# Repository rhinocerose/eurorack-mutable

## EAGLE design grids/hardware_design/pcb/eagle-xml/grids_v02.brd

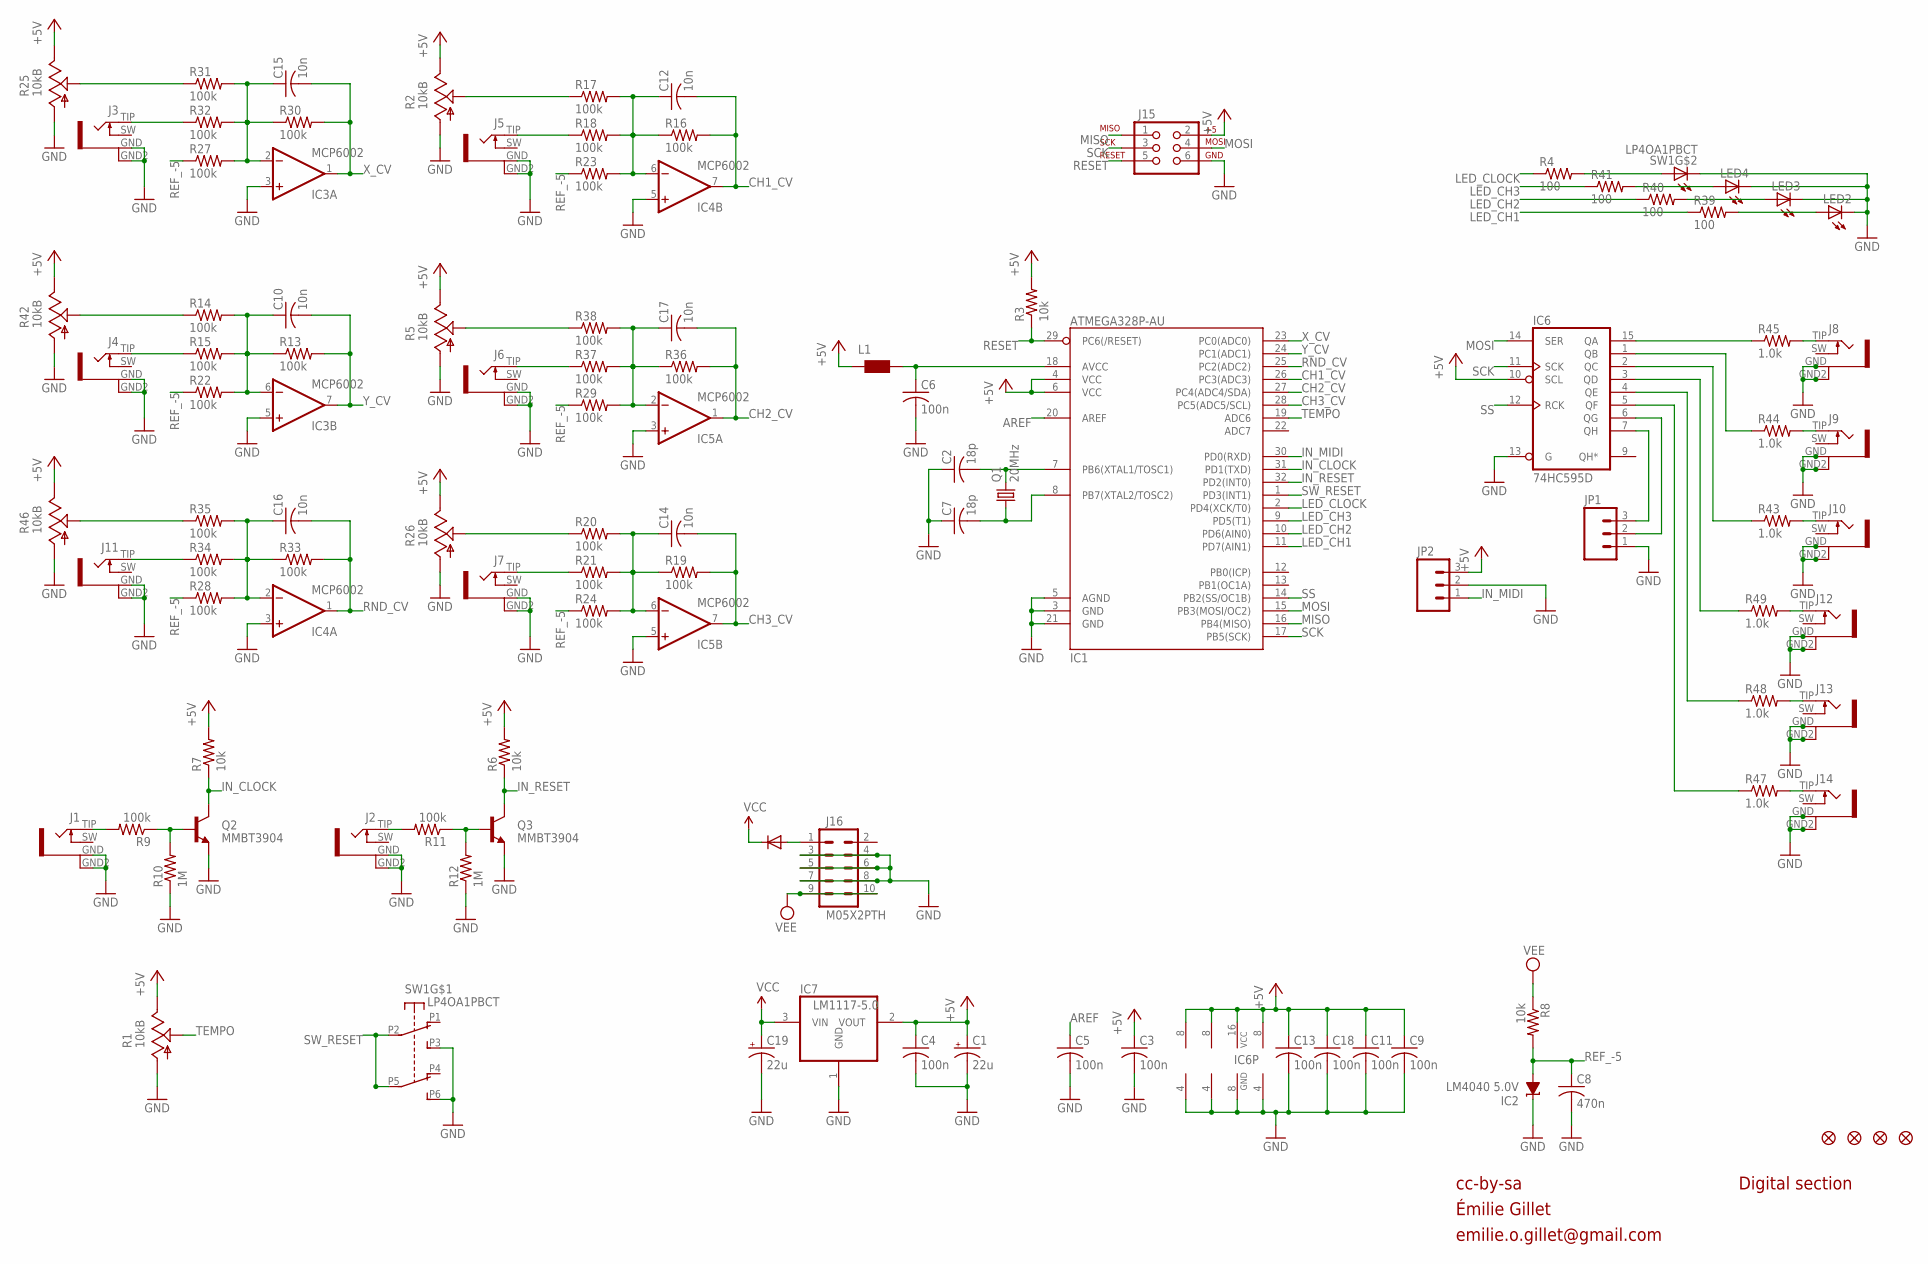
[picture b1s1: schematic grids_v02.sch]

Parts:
C1, C19: 22u; PANASONIC_C
C2, C7: 18p; C0603
C3, C4, C5, C6, C9, C11, C13, C18: 100n; C0603
C8: 470n; C0603
C10, C12, C14, C15, C16, C17: 10n; C0603
D1: 1N5819HW; SOD123
F1, F2, F3, F4: FIDUCIAL1X2; FIDUCIAL-1X2
IC1: ATMEGA328P-AU; TQFP32-08
IC2: LM4040 5.0V; DBZ_R-PDSO-G3
IC3, IC4, IC5: MCP6002; SO08
IC6: 74HC595D; SO16
IC7: LM1117-5.0; SOT223
J1, J2, J3, J4, J5, J6, J7, J8, J9, J10, J11, J12, J13, J14: PJ301WQP; WQP_PJ_301BM
J15: AVR_SPI_PRG_6PTH; 2X3
J16: M05X2PTH; AVR_ICSP
JP1, JP2: M03PTH; 1X03
L1: WE-CBF_0603; 0603
LED2, LED3, LED4: LED3MM
Q1: 20MHz; HC49UP
Q2, Q3: MMBT3904; SOT23-BEC
R1, R2, R5, R25, R26, R46: 10kB; ALPS_POT_VERTICAL_PS
R3, R6, R7, R8: 10k; R0603
R4, R39, R40, R41: 100; R0603
R9, R11, R13, R14, R15, R16, R17, R18, R19, R20, R21, R22, R23, R24, R27, R28, R29, R30, R31, R32, R33, R34, R35, R36, R37, R38: 100k; R0603
R10, R12: 1M; R0603
R42: 10kB; ALPS_POT_VERTICAL_PS4
R43, R44, R45, R47, R48, R49: 1.0k; R0603
SW1: LP4OA1PBCT

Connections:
+5V: C1.+, C3.1, C4.1, C9.1, C11.1, C13.1, C18.1, IC1.4 (VCC), IC1.6 (VCC), IC3.8 (V+), IC4.8 (V+), IC5.8 (V+), IC6.10 (SCL), IC6.16 (VCC), IC7.2 (VOUT), J15.2, JP2.3, L1.1, R1.P$1 (E), R2.P$1 (E), R3.2, R5.P$1 (E), R6.2, R7.2, R25.P$1 (E), R26.P$1 (E), R42.P$1 (E), R46.P$1 (E)
AREF: C5.1, IC1.20 (AREF)
CH1_CV: C12.2, IC1.26 (PC3(ADC3)), IC4.7 (OUT), R16.2
CH2_CV: C17.2, IC1.27 (PC4(ADC4/SDA)), IC5.1 (OUT), R36.2
CH3_CV: C14.2, IC1.28 (PC5(ADC5/SCL)), IC5.7 (OUT), R19.2
CLOCK_OUT: IC6.6 (QG), JP1.2
GATE1_IN: J1.TIP (2), R9.2
GATE1_LED: R4.2, SW1.L1
GATE2_IN: J2.TIP (2), R11.2
GATE2_LED: LED4.A, R41.2
GATE3_LED: LED3.A, R40.2
GATE4_LED: LED2.A, R39.2
GND: C1.-, C2.1, C3.2, C4.2, C5.2, C6.2, C7.1, C8.2, C9.2, C11.2, C13.2, C18.2, C19.-, IC1.3 (GND), IC1.5 (AGND), IC1.21 (GND), IC2.1 (C), IC3.3 (+IN), IC3.4 (V-), IC3.5 (+IN), IC4.3 (+IN), IC4.4 (V-), IC4.5 (+IN), IC5.3 (+IN), IC5.4 (V-), IC5.5 (+IN), IC6.8 (GND), IC6.13 (G), IC7.1 (GND), J1.GND (1), J1.GND2 (4), J2.GND (1), J2.GND2 (4), J3.GND (1), J3.GND2 (4), J4.GND (1), J4.GND2 (4), J5.GND (1), J5.GND2 (4), J6.GND (1), J6.GND2 (4), J7.GND (1), J7.GND2 (4), J8.GND (1), J8.GND2 (4), J9.GND (1), J9.GND2 (4), J10.GND (1), J10.GND2 (4), J11.GND (1), J11.GND2 (4), J12.GND (1), J12.GND2 (4), J13.GND (1), J13.GND2 (4), J14.GND (1), J14.GND2 (4), J15.6, J16.3, J16.4, J16.5, J16.6, J16.7, J16.8, JP1.1, JP2.2, LED2.K (C), LED3.K (C), LED4.K (C), Q2.E, Q3.E, R1.P$3 (A), R2.P$3 (A), R5.P$3 (A), R10.1, R12.1, R25.P$3 (A), R26.P$3 (A), R42.P$3 (A), R46.P$3 (A), SW1.L2, SW1.P3 (A3), SW1.P6 (B3)
IN_CLOCK: IC1.31 (PD1(TXD)), Q2.C, R7.1
IN_MIDI: IC1.30 (PD0(RXD)), JP2.1
IN_RESET: IC1.32 (PD2(INT0)), Q3.C, R6.1
LED_CH1: IC1.11 (PD7(AIN1)), R39.1
LED_CH2: IC1.10 (PD6(AIN0)), R40.1
LED_CH3: IC1.9 (PD5(T1)), R41.1
LED_CLOCK: IC1.2 (PD4(XCK/T0)), R4.1
MISO: IC1.16 (PB4(MISO)), J15.1
MOSI: IC1.15 (PB3(MOSI/OC2)), IC6.14 (SER), J15.4
unnamed: Q2.B, R9.1, R10.2
unnamed: Q3.B, R11.1, R12.2
unnamed: D1.A, J16.1
unnamed: J14.TIP (2), R47.2
unnamed: J13.TIP (2), R48.2
unnamed: J12.TIP (2), R49.2
unnamed: R25.P$2 (S), R31.1
unnamed: J3.TIP (2), R32.1
unnamed: C10.1, IC3.6 (-IN), R13.1, R14.2, R15.2, R22.2
unnamed: R14.1, R42.P$2 (S)
unnamed: J4.TIP (2), R15.1
unnamed: C16.1, IC4.2 (-IN), R28.2, R33.1, R34.2, R35.2
unnamed: R35.1, R46.P$2 (S)
unnamed: J11.TIP (2), R34.1
unnamed: C12.1, IC4.6 (-IN), R16.1, R17.2, R18.2, R23.2
unnamed: R2.P$2 (S), R17.1
unnamed: J5.TIP (2), R18.1
unnamed: C17.1, IC5.2 (-IN), R29.2, R36.1, R37.2, R38.2
unnamed: R5.P$2 (S), R38.1
unnamed: J6.TIP (2), R37.1
unnamed: C14.1, IC5.6 (-IN), R19.1, R20.2, R21.2, R24.2
unnamed: R20.1, R26.P$2 (S)
unnamed: J7.TIP (2), R21.1
unnamed: IC6.15 (QA), R45.1
unnamed: IC6.1 (QB), R44.1
unnamed: C15.1, IC3.2 (-IN), R27.2, R30.1, R31.2, R32.2
unnamed: IC6.2 (QC), R43.1
unnamed: IC6.3 (QD), R49.1
unnamed: IC6.4 (QE), R48.1
unnamed: IC6.5 (QF), R47.1
unnamed: J8.TIP (2), R45.2
unnamed: J9.TIP (2), R44.2
unnamed: J10.TIP (2), R43.2
unnamed: C6.1, IC1.18 (AVCC), L1.2
unnamed: C7.2, IC1.8 (PB7(XTAL2/TOSC2)), Q1.1
unnamed: C2.2, IC1.7 (PB6(XTAL1/TOSC1)), Q1.2
RANDOM_GATE: IC6.7 (QH), JP1.3
REF_-5: C8.1, IC2.2 (A), R8.2, R22.1, R23.1, R24.1, R27.1, R28.1, R29.1
RESET: IC1.29 (PC6(/RESET)), J15.5, R3.1
RND_CV: C16.2, IC1.25 (PC2(ADC2)), IC4.1 (OUT), R33.2
SCK: IC1.17 (PB5(SCK)), IC6.11 (SCK), J15.3
SS: IC1.14 (PB2(SS/OC1B)), IC6.12 (RCK)
SW_RESET: IC1.1 (PD3(INT1)), SW1.P2 (A2), SW1.P5 (B2)
TEMPO: IC1.19 (ADC6), R1.P$2 (S)
VCC: C19.+, D1.C, IC7.3 (VIN)
VEE: J16.9, J16.10, R8.1
X_CV: C15.2, IC1.23 (PC0(ADC0)), IC3.1 (OUT), R30.2
Y_CV: C10.2, IC1.24 (PC1(ADC1)), IC3.7 (OUT), R13.2

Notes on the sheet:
cc-by-sa
Digital section
Émilie Gillet
emilie.o.gillet@gmail.com

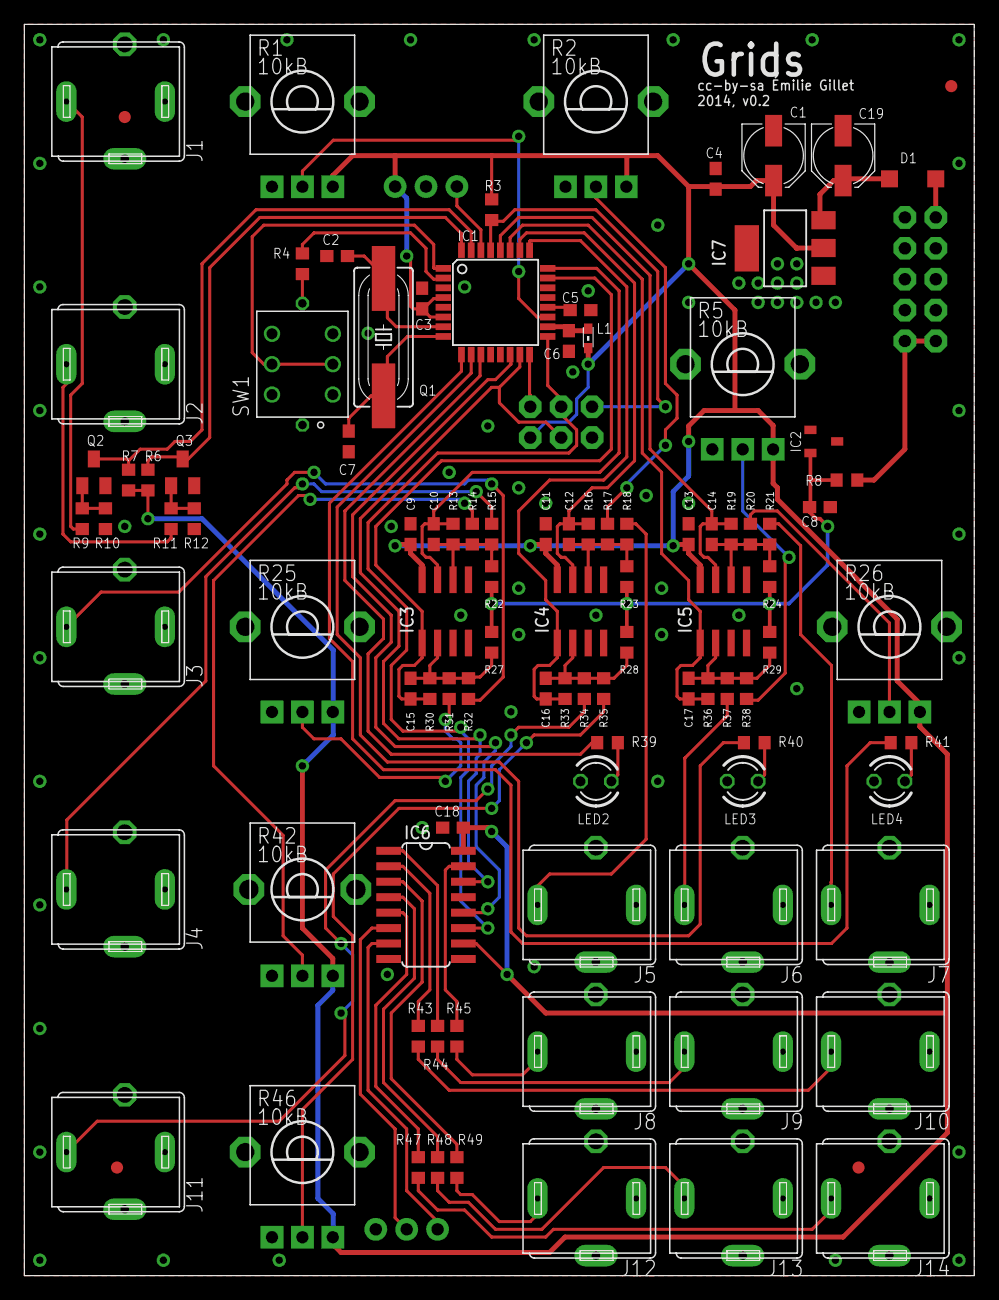
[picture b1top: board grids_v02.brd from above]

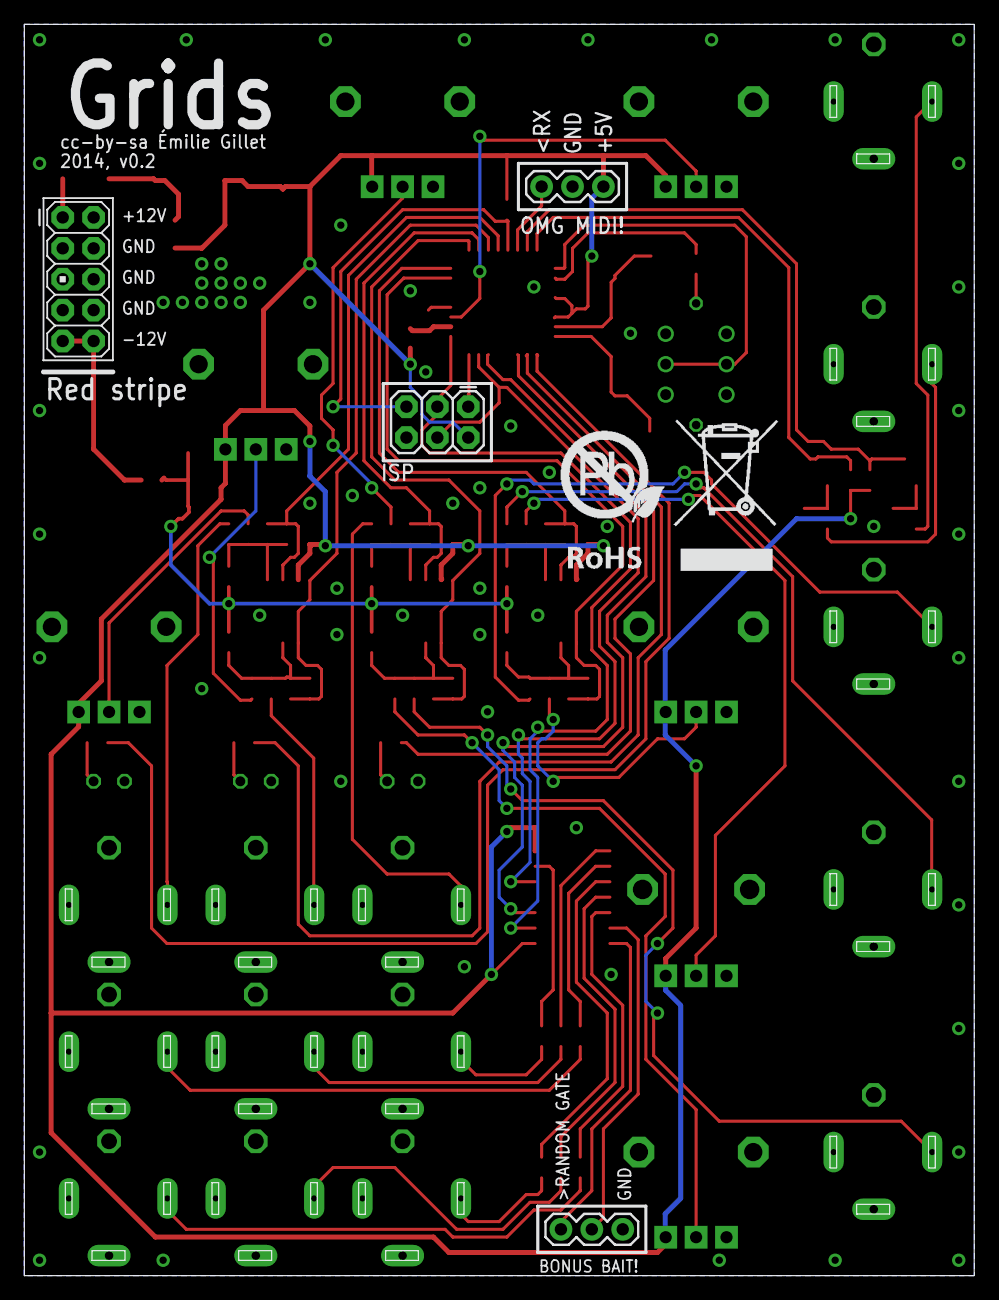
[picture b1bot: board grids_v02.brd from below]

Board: 2 copper layers, 78.1 x 102.9 mm, 108 parts (5 on the bottom side), 70 nets.

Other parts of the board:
U$1: EURORACK_TEMPLATE
U$2: ROHS_BIG

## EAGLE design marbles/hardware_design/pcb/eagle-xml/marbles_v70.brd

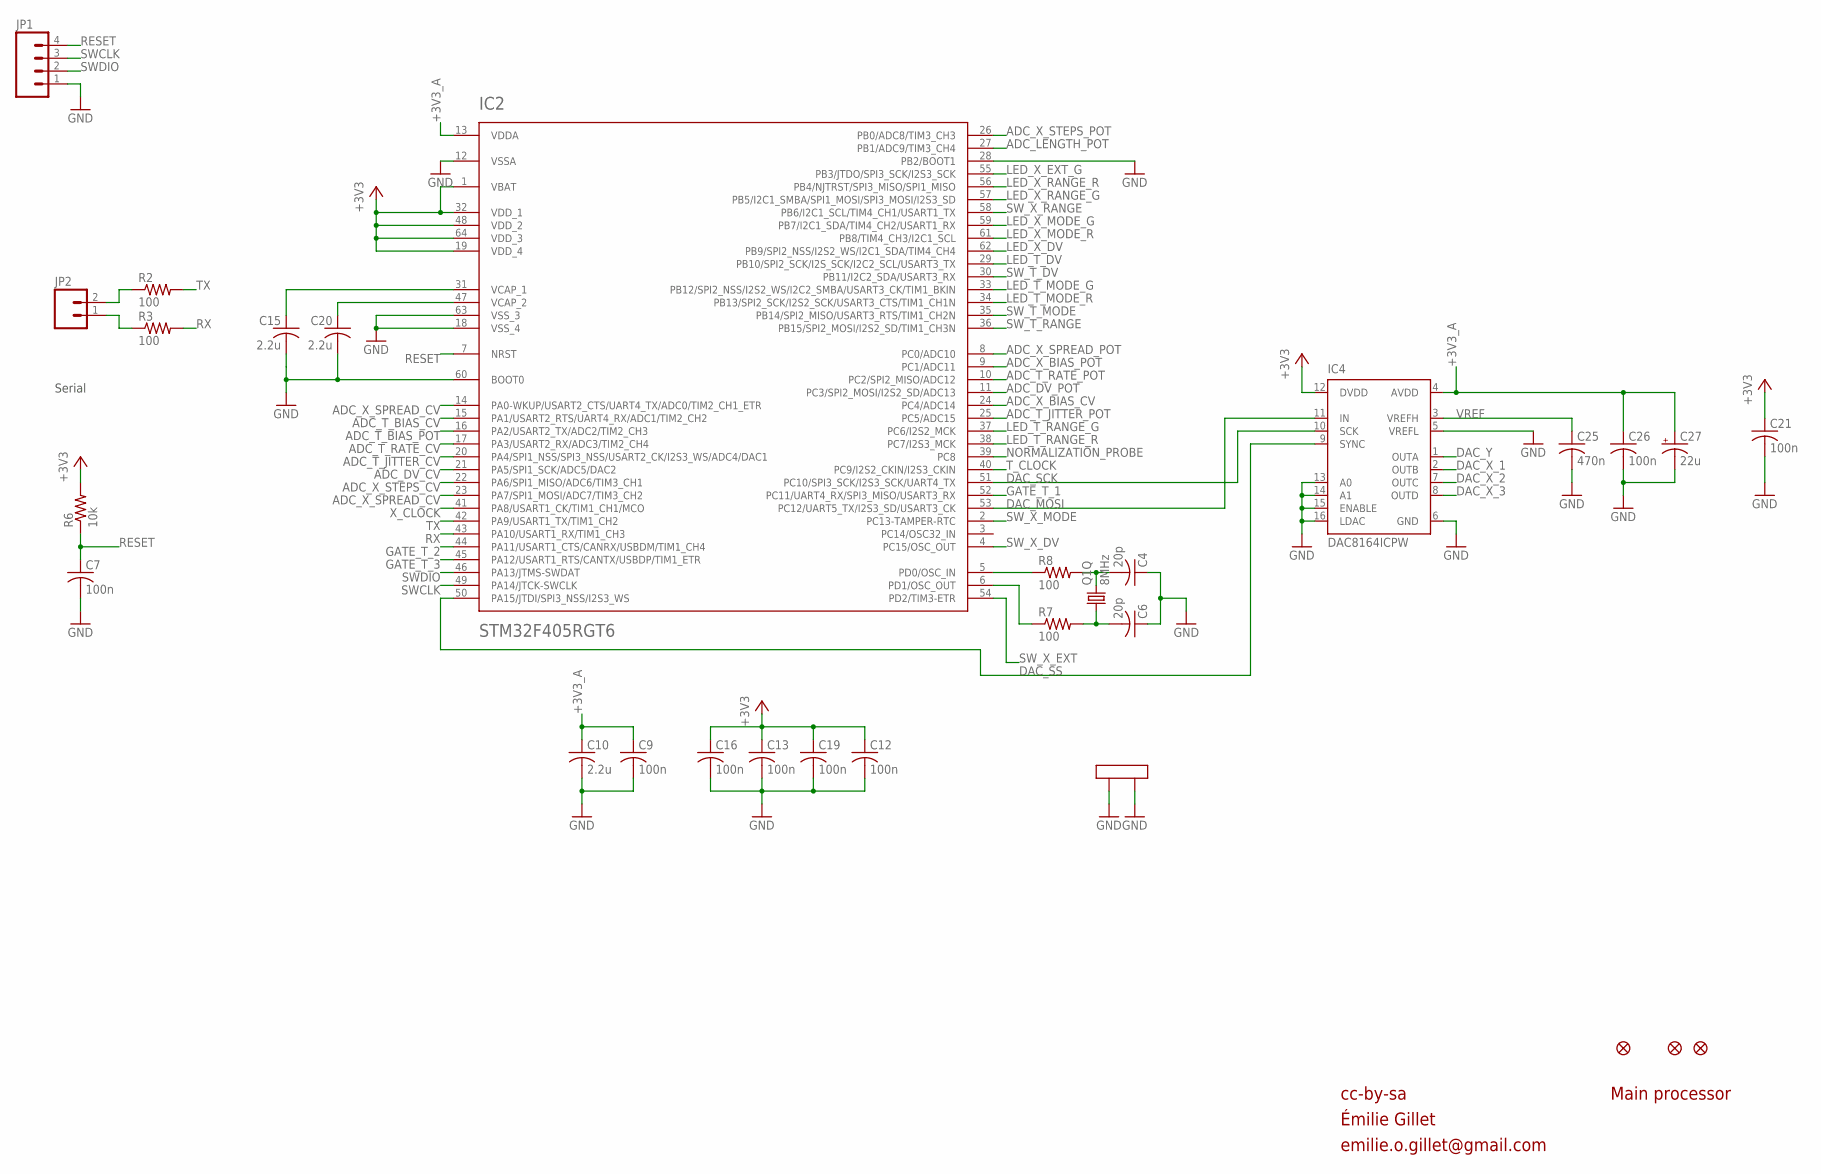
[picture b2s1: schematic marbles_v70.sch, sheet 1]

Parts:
C4, C6: 20p; C0402
C7, C9, C12, C13, C16, C19, C21, C26: 100n; C0402
C10, C15, C20: 2.2u; C0805
C25: 470n; C0402
C27: 22u; PANASONIC_C
F1, F2, F3: FIDUCIAL1X2; FIDUCIAL-1X2
IC2: STM32F405RGT6; TQFP-10X10-64
IC4: DAC8164ICPW; SOP65P640X110-16N
JP1: M04PTH; 1X04
JP2: M02PTH; 1X02
Q1: 8MHz; CTS406
R2, R3, R7, R8: 100; R0402
R6: 10k; R0402

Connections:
+3V3: C12.1, C13.1, C16.1, C19.1, C21.1, IC2.1 (VBAT), IC2.19 (VDD_4), IC2.32 (VDD_1), IC2.48 (VDD_2), IC2.64 (VDD_3), IC4.12 (DVDD), R6.2; also elsewhere on the board
+3V3_A: C9.1, C10.1, C26.1, C27.+, IC2.13 (VDDA), IC4.4 (AVDD); also elsewhere on the board
ADC_DV_CV: IC2.21 (PA5/SPI1_SCK/ADC5/DAC2); also elsewhere on the board
ADC_DV_POT: IC2.11 (PC3/SPI2_MOSI/I2S2_SD/ADC13); also elsewhere on the board
ADC_LENGTH_POT: IC2.27 (PB1/ADC9/TIM3_CH4); also elsewhere on the board
ADC_T_BIAS_CV: IC2.15 (PA1/USART2_RTS/UART4_RX/ADC1/TIM2_CH2); also elsewhere on the board
ADC_T_BIAS_POT: IC2.16 (PA2/USART2_TX/ADC2/TIM2_CH3); also elsewhere on the board
ADC_T_JITTER_CV: IC2.20 (PA4/SPI1_NSS/SPI3_NSS/USART2_CK/I2S3_WS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); also elsewhere on the board
ADC_T_JITTER_POT: IC2.25 (PC5/ADC15); also elsewhere on the board
ADC_T_RATE_CV: IC2.17 (PA3/USART2_RX/ADC3/TIM2_CH4); also elsewhere on the board
ADC_T_RATE_POT: IC2.10 (PC2/SPI2_MISO/ADC12); also elsewhere on the board
ADC_X_BIAS_CV: IC2.24 (PC4/ADC14); also elsewhere on the board
ADC_X_BIAS_POT: IC2.9 (PC1/ADC11); also elsewhere on the board
ADC_X_SPREAD_CV: IC2.14 (PA0-WKUP/USART2_CTS/UART4_TX/ADC0/TIM2_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), IC2.23 (PA7/SPI1_MOSI/ADC7/TIM3_CH2); also elsewhere on the board
ADC_X_SPREAD_POT: IC2.8 (PC0/ADC10); also elsewhere on the board
ADC_X_STEPS_CV: IC2.22 (PA6/SPI1_MISO/ADC6/TIM3_CH1); also elsewhere on the board
ADC_X_STEPS_POT: IC2.26 (PB0/ADC8/TIM3_CH3); also elsewhere on the board
DAC_MOSI: IC2.53 (PC12/UART5_TX/I2S3_SD/USART3_CK), IC4.11 (IN)
DAC_SCK: IC2.51 (PC10/SPI3_SCK/I2S3_SCK/UART4_TX), IC4.10 (SCK)
DAC_SS: IC2.50 (PA15/JTDI/SPI3_NSS/I2S3_WS), IC4.9 (SYNC)
DAC_X_1: IC4.2 (OUTB); also elsewhere on the board
DAC_X_2: IC4.7 (OUTC); also elsewhere on the board
DAC_X_3: IC4.8 (OUTD); also elsewhere on the board
DAC_Y: IC4.1 (OUTA); also elsewhere on the board
GATE_T_1: IC2.52 (PC11/UART4_RX/SPI3_MISO/USART3_RX); also elsewhere on the board
GATE_T_2: IC2.44 (PA11/USART1_CTS/CANRX/USBDM/TIM1_CH4); also elsewhere on the board
GATE_T_3: IC2.45 (PA12/USART1_RTS/CANTX/USBDP/TIM1_ETR); also elsewhere on the board
GND: C4.1, C6.1, C7.2, C9.2, C10.2, C12.2, C13.2, C15.2, C16.2, C19.2, C20.2, C21.2, C25.2, C26.2, C27.-, IC2.12 (VSSA), IC2.18 (VSS_4), IC2.28 (PB2/BOOT1), IC2.60 (BOOT0), IC2.63 (VSS_3), IC4.5 (VREFL), IC4.6 (GND), IC4.13 (A0), IC4.14 (A1), IC4.15 (ENABLE), IC4.16 (LDAC), JP1.1, Q1.2 (LID1), Q1.4 (LID2); also elsewhere on the board
LED_T_DV: IC2.29 (PB10/SPI2_SCK/I2S_SCK/I2C2_SCL/USART3_TX); also elsewhere on the board
LED_T_MODE_G: IC2.33 (PB12/SPI2_NSS/I2S2_WS/I2C2_SMBA/USART3_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); also elsewhere on the board
LED_T_MODE_R: IC2.34 (PB13/SPI2_SCK/I2S2_SCK/USART3_CTS/TIM1_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); also elsewhere on the board
LED_T_RANGE_G: IC2.37 (PC6/I2S2_MCK); also elsewhere on the board
LED_T_RANGE_R: IC2.38 (PC7/I2S3_MCK); also elsewhere on the board
LED_X_DV: IC2.62 (PB9/SPI2_NSS/I2S2_WS/I2C1_SDA/TIM4_CH4); also elsewhere on the board
LED_X_EXT_G: IC2.55 (PB3/JTDO/SPI3_SCK/I2S3_SCK); also elsewhere on the board
LED_X_MODE_G: IC2.59 (PB7/I2C1_SDA/TIM4_CH2/USART1_RX); also elsewhere on the board
LED_X_MODE_R: IC2.61 (PB8/TIM4_CH3/I2C1_SCL); also elsewhere on the board
LED_X_RANGE_G: IC2.57 (PB5/I2C1_SMBA/SPI1_MOSI/SPI3_MOSI/I2S3_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); also elsewhere on the board
LED_X_RANGE_R: IC2.56 (PB4/NJTRST/SPI3_MISO/SPI1_MISO); also elsewhere on the board
unnamed: IC2.6 (PD1/OSC_OUT), R7.1
unnamed: IC2.5 (PD0/OSC_IN), R8.1
unnamed: C20.1, IC2.47 (VCAP_2)
unnamed: C15.1, IC2.31 (VCAP_1)
unnamed: JP2.2, R2.1
unnamed: JP2.1, R3.1
unnamed: C4.2, Q1.3 (2), R8.2
unnamed: C6.2, Q1.1, R7.2
NORMALIZATION_PROBE: IC2.39 (PC8); also elsewhere on the board
RESET: C7.1, IC2.7 (NRST), JP1.4, R6.1
RX: IC2.43 (PA10/USART1_RX/TIM1_CH3), R3.2
SWCLK: IC2.49 (PA14/JTCK-SWCLK), JP1.3
SWDIO: IC2.46 (PA13/JTMS-SWDAT), JP1.2
SW_T_DV: IC2.30 (PB11/I2C2_SDA/USART3_RX); also elsewhere on the board
SW_T_MODE: IC2.35 (PB14/SPI2_MISO/USART3_RTS/TIM1_CH2N); also elsewhere on the board
SW_T_RANGE: IC2.36 (PB15/SPI2_MOSI/I2S2_SD/TIM1_CH3N); also elsewhere on the board
SW_X_DV: IC2.4 (PC15/OSC_OUT); also elsewhere on the board
SW_X_EXT: IC2.54 (PD2/TIM3-ETR); also elsewhere on the board
SW_X_MODE: IC2.2 (PC13-TAMPER-RTC); also elsewhere on the board
SW_X_RANGE: IC2.58 (PB6/I2C1_SCL/TIM4_CH1/USART1_TX); also elsewhere on the board
TX: IC2.42 (PA9/USART1_TX/TIM1_CH2), R2.2
T_CLOCK: IC2.40 (PC9/I2S2_CKIN/I2S3_CKIN); also elsewhere on the board
VREF: C25.1, IC4.3 (VREFH); also elsewhere on the board
X_CLOCK: IC2.41 (PA8/USART1_CK/TIM1_CH1/MCO); also elsewhere on the board

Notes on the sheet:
cc-by-sa
Main processor
Serial
Émilie Gillet
emilie.o.gillet@gmail.com

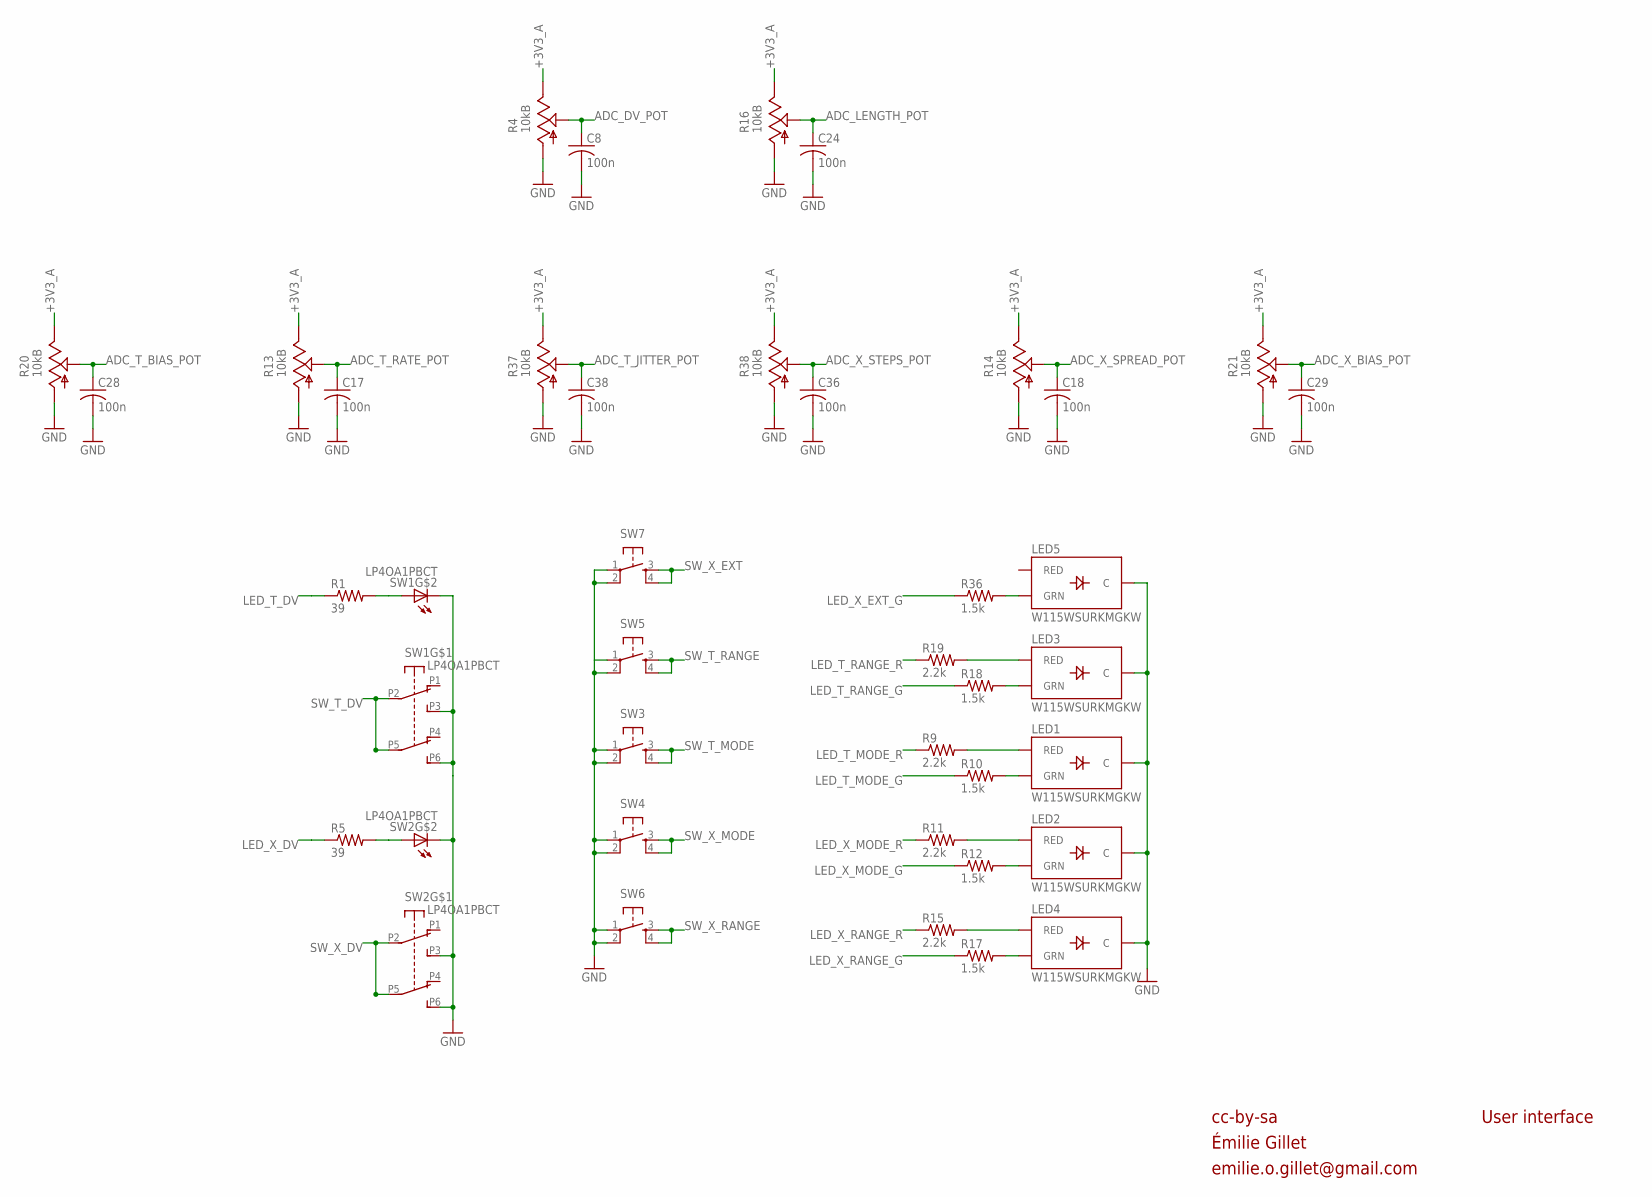
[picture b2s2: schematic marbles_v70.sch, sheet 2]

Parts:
C8, C17, C18, C24, C28, C29, C36, C38: 100n; C0402
LED1, LED2, LED3, LED4, LED5: W115WSURKMGKW; LED-BICOLOR-THROUGHHOLE-2.54
R1, R5: 39; R0402
R4, R13, R14, R16, R20, R21, R37, R38: 10kB; ALPS_POT_VERTICAL_PS
R9, R11, R15, R19: 2.2k; R0402
R10, R12, R17, R18, R36: 1.5k; R0402
SW1, SW2: LP4OA1PBCT
SW3, SW4, SW5, SW6, SW7: TAC_SWITCHPTH; TACTILE-PTH

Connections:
+3V3_A: R4.P$1 (E), R13.P$1 (E), R14.P$1 (E), R16.P$1 (E), R20.P$1 (E), R21.P$1 (E), R37.P$1 (E), R38.P$1 (E); also elsewhere on the board
ADC_DV_POT: C8.1, R4.P$2 (S); also elsewhere on the board
ADC_LENGTH_POT: C24.1, R16.P$2 (S); also elsewhere on the board
ADC_T_BIAS_POT: C28.1, R20.P$2 (S); also elsewhere on the board
ADC_T_JITTER_POT: C38.1, R37.P$2 (S); also elsewhere on the board
ADC_T_RATE_POT: C17.1, R13.P$2 (S); also elsewhere on the board
ADC_X_BIAS_POT: C29.1, R21.P$2 (S); also elsewhere on the board
ADC_X_SPREAD_POT: C18.1, R14.P$2 (S); also elsewhere on the board
ADC_X_STEPS_POT: C36.1, R38.P$2 (S); also elsewhere on the board
GND: C8.2, C17.2, C18.2, C24.2, C28.2, C29.2, C36.2, C38.2, LED1.2 (C), LED2.2 (C), LED3.2 (C), LED4.2 (C), LED5.2 (C), R4.P$3 (A), R13.P$3 (A), R14.P$3 (A), R16.P$3 (A), R20.P$3 (A), R21.P$3 (A), R37.P$3 (A), R38.P$3 (A), SW1.L2, SW1.P3 (A3), SW1.P6 (B3), SW2.L2, SW2.P3 (A3), SW2.P6 (B3), SW3.1, SW3.2, SW4.1, SW4.2, SW5.1, SW5.2, SW6.1, SW6.2, SW7.1, SW7.2; also elsewhere on the board
LED_T_DV: R1.1; also elsewhere on the board
LED_T_MODE_G: R10.1; also elsewhere on the board
LED_T_MODE_R: R9.1; also elsewhere on the board
LED_T_RANGE_G: R18.1; also elsewhere on the board
LED_T_RANGE_R: R19.1; also elsewhere on the board
LED_X_DV: R5.1; also elsewhere on the board
LED_X_EXT_G: R36.1; also elsewhere on the board
LED_X_MODE_G: R12.1; also elsewhere on the board
LED_X_MODE_R: R11.1; also elsewhere on the board
LED_X_RANGE_G: R17.1; also elsewhere on the board
LED_X_RANGE_R: R15.1; also elsewhere on the board
unnamed: R1.2, SW1.L1
unnamed: R5.2, SW2.L1
unnamed: LED3.3 (RED), R19.2
unnamed: LED3.1 (GRN), R18.2
unnamed: LED1.3 (RED), R9.2
unnamed: LED2.3 (RED), R11.2
unnamed: LED2.1 (GRN), R12.2
unnamed: LED4.3 (RED), R15.2
unnamed: LED1.1 (GRN), R10.2
unnamed: LED4.1 (GRN), R17.2
unnamed: LED5.1 (GRN), R36.2
SW_T_DV: SW1.P2 (A2), SW1.P5 (B2); also elsewhere on the board
SW_T_MODE: SW3.3, SW3.4; also elsewhere on the board
SW_T_RANGE: SW5.3, SW5.4; also elsewhere on the board
SW_X_DV: SW2.P2 (A2), SW2.P5 (B2); also elsewhere on the board
SW_X_EXT: SW7.3, SW7.4; also elsewhere on the board
SW_X_MODE: SW4.3, SW4.4; also elsewhere on the board
SW_X_RANGE: SW6.3, SW6.4; also elsewhere on the board

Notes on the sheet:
cc-by-sa
User interface
Émilie Gillet
emilie.o.gillet@gmail.com

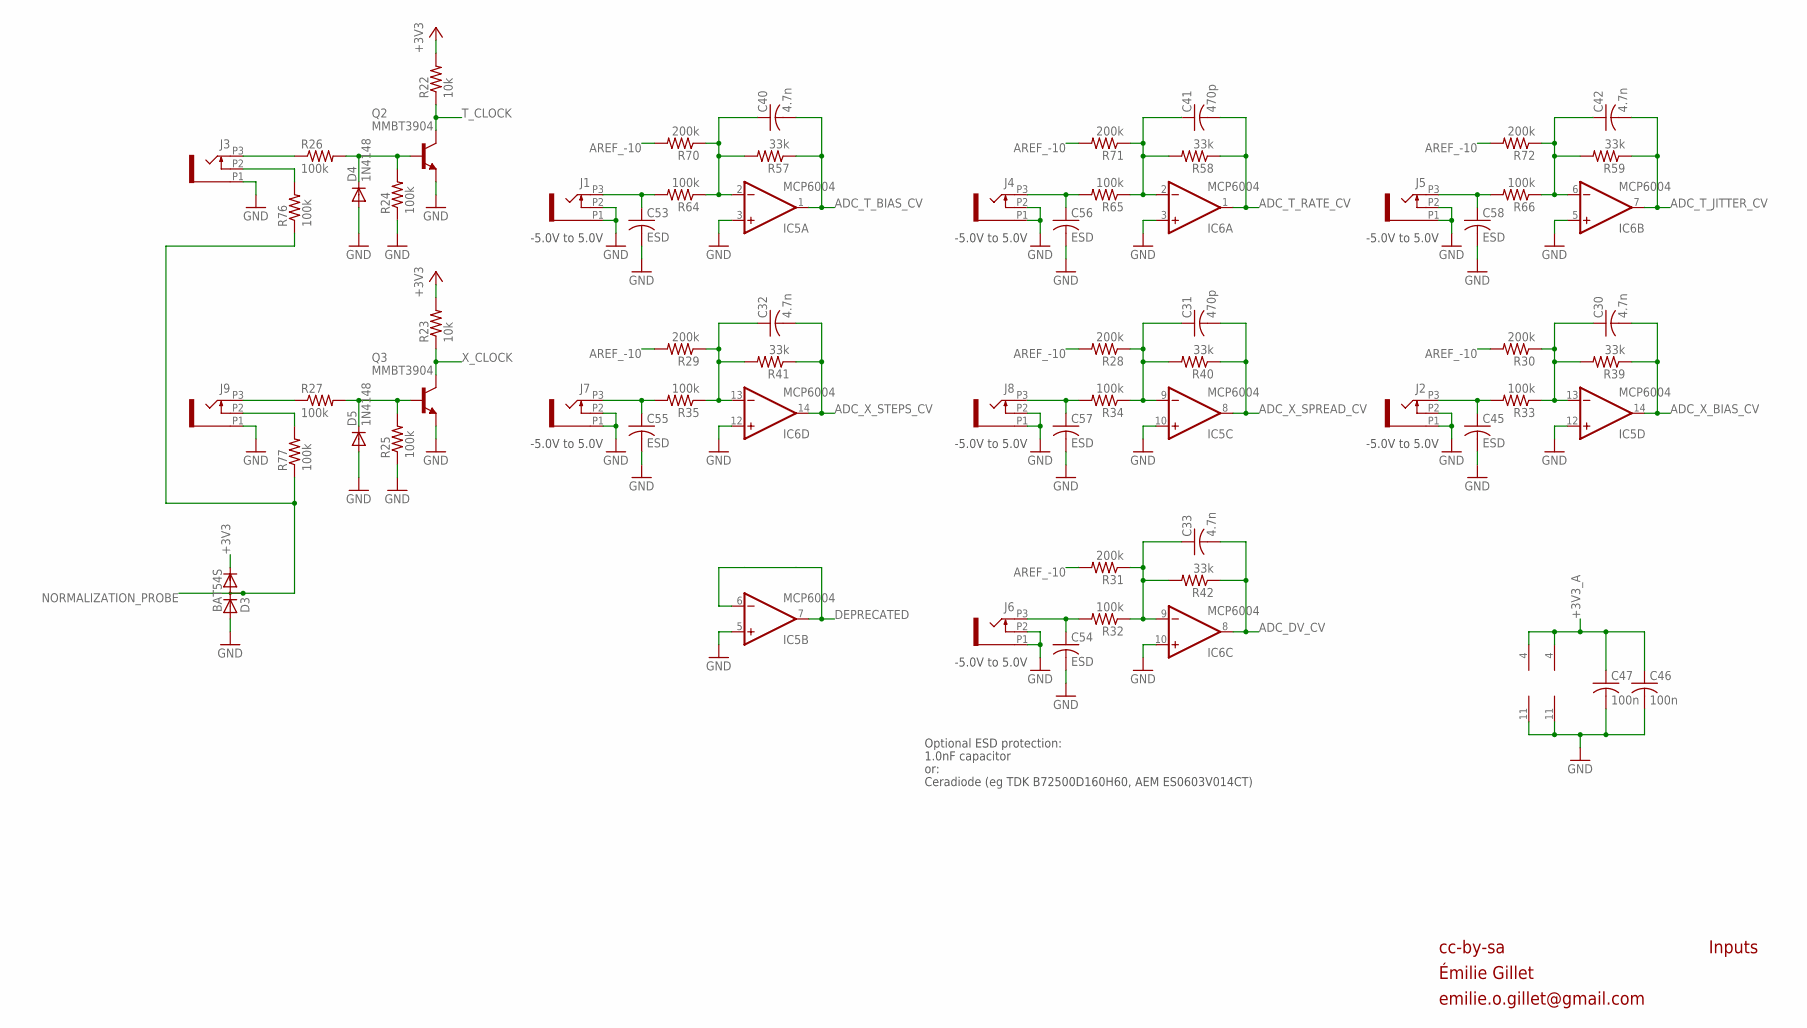
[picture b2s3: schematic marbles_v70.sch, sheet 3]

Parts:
C30, C32, C33, C40, C42: 4.7n; C0402
C31, C41: 470p; C0402
C45, C53, C54, C55, C56, C57, C58: ESD; C0603
C46, C47: 100n; C0402
D3: BAT54S; SOT23
D4, D5: 1N4148; SOD523
IC5, IC6: MCP6004; TSSOP14_065
J1, J2, J3, J4, J5, J6, J7, J8, J9: PJ301_THONKICONN6; WQP_PJ_301M6
Q2, Q3: MMBT3904; SOT23-BEC
R22, R23: 10k; R0402
R24, R25, R26, R27, R32, R33, R34, R35, R64, R65, R66, R76, R77: 100k; R0402
R28, R29, R30, R31, R70, R71, R72: 200k; R0402
R39, R40, R41, R42, R57, R58, R59: 33k; R0402

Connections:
+3V3: D3.2 (C), R22.2, R23.2; also elsewhere on the board
+3V3_A: C46.1, C47.1, IC5.4 (V+), IC6.4 (V+); also elsewhere on the board
ADC_DV_CV: C33.2, IC6.8 (OUT), R42.1; also elsewhere on the board
ADC_T_BIAS_CV: C40.2, IC5.1 (OUT), R57.1; also elsewhere on the board
ADC_T_JITTER_CV: C42.2, IC6.7 (OUT), R59.1; also elsewhere on the board
ADC_T_RATE_CV: C41.2, IC6.1 (OUT), R58.1; also elsewhere on the board
ADC_X_BIAS_CV: C30.2, IC5.14 (OUT), R39.1; also elsewhere on the board
ADC_X_SPREAD_CV: C31.2, IC5.8 (OUT), R40.1; also elsewhere on the board
ADC_X_STEPS_CV: C32.2, IC6.14 (OUT), R41.1; also elsewhere on the board
AREF_-10: R28.2, R29.2, R30.2, R31.2, R70.2, R71.2, R72.2; also elsewhere on the board
DEPRECATED: IC5.6 (-IN), IC5.7 (OUT)
GND: C45.2, C46.2, C47.2, C53.2, C54.2, C55.2, C56.2, C57.2, C58.2, D3.1 (A), D4.A, D5.A, IC5.3 (+IN), IC5.5 (+IN), IC5.10 (+IN), IC5.11 (V-), IC5.12 (+IN), IC6.3 (+IN), IC6.5 (+IN), IC6.10 (+IN), IC6.11 (V-), IC6.12 (+IN), J1.P1 (1), J1.P2 (2), J2.P1 (1), J2.P2 (2), J3.P1 (1), J4.P1 (1), J4.P2 (2), J5.P1 (1), J5.P2 (2), J6.P1 (1), J6.P2 (2), J7.P1 (1), J7.P2 (2), J8.P1 (1), J8.P2 (2), J9.P1 (1), Q2.E, Q3.E, R24.1, R25.1; also elsewhere on the board
MORPH_IN: C53.1, J1.P3 (3), R64.2
MORPH_IN1: C55.1, J7.P3 (3), R35.2
MORPH_IN3: C56.1, J4.P3 (3), R65.2
MORPH_IN4: C57.1, J8.P3 (3), R34.2
MORPH_IN5: C54.1, J6.P3 (3), R32.2
MORPH_IN6: C58.1, J5.P3 (3), R66.2
MORPH_IN7: C45.1, J2.P3 (3), R33.2
unnamed: C41.1, IC6.2 (-IN), R58.2, R65.1, R71.1
unnamed: C40.1, IC5.2 (-IN), R57.2, R64.1, R70.1
unnamed: C42.1, IC6.6 (-IN), R59.2, R66.1, R72.1
unnamed: C31.1, IC5.9 (-IN), R28.1, R34.1, R40.2
unnamed: C30.1, IC5.13 (-IN), R30.1, R33.1, R39.2
unnamed: C32.1, IC6.13 (-IN), R29.1, R35.1, R41.2
unnamed: C33.1, IC6.9 (-IN), R31.1, R32.1, R42.2
unnamed: J9.P3 (3), R27.1
unnamed: J9.P2 (2), R77.2
unnamed: J3.P2 (2), R76.2
unnamed: D4.C, Q2.B, R24.2, R26.2
unnamed: D5.C, Q3.B, R25.2, R27.2
unnamed: J3.P3 (3), R26.1
NORMALIZATION_PROBE: D3.3 (AC), R76.1, R77.1; also elsewhere on the board
T_CLOCK: Q2.C, R22.1; also elsewhere on the board
X_CLOCK: Q3.C, R23.1; also elsewhere on the board

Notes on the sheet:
cc-by-sa
Inputs
-5.0V to 5.0V
Optional ESD protection:
1.0nF capacitor
or:
Ceradiode (eg TDK B72500D160H60, AEM ES0603V014CT)
Émilie Gillet
emilie.o.gillet@gmail.com

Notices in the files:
braids/hardware_design/pcb/eagle-xml/braids_v50.brd:
cc-by-sa Émilie Gillet, 2015. v5
clouds/hardware_design/pcb/eagle-xml/clouds_v30.brd:
cc-by-sa Émilie Gillet, 2015. v3
stages/hardware_design/pcb/eagle-xml/stages_v70.brd:
v7 cc-by-sa Émilie Gillet 2017
